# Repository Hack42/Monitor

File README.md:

# Monitor
Monitor electric power and indoor climate
Initial Version

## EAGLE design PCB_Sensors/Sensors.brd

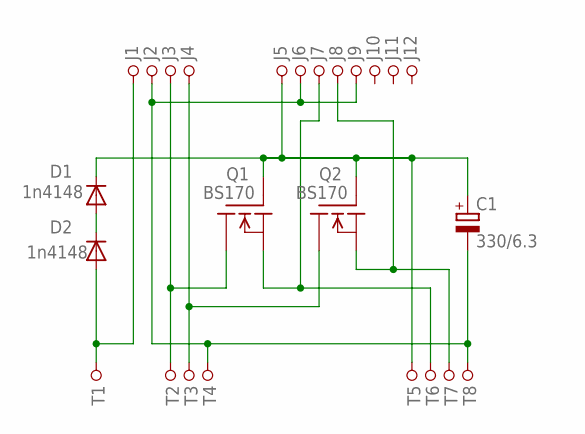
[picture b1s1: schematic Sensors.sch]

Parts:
C1: 330/6.3; E2,5-6
D1, D2: 1n4148; DO34Z7
J1, J2, J3, J4, J5, J6, J7, J8, J9, J10, J11, J12: PINHDR-1X1; HDR1X1
Q1, Q2: BS170; TO92
T1, T2, T3, T4, T5, T6, T7, T8: PINHDR-1X1; HDR1X1

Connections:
unnamed: C1.+, D1.C, J5.1, Q1.2 (G), Q2.2 (G), T5.1
unnamed: C1.-, J2.1, J6.1, J9.1, T4.1, T8.1
unnamed: D2.A, J1.1, T1.1
unnamed: D1.A, D2.C
unnamed: J3.1, Q1.3 (D), T2.1
unnamed: J4.1, Q2.3 (D), T3.1
unnamed: J7.1, Q1.1 (S), T6.1
unnamed: J8.1, Q2.1 (S), T7.1

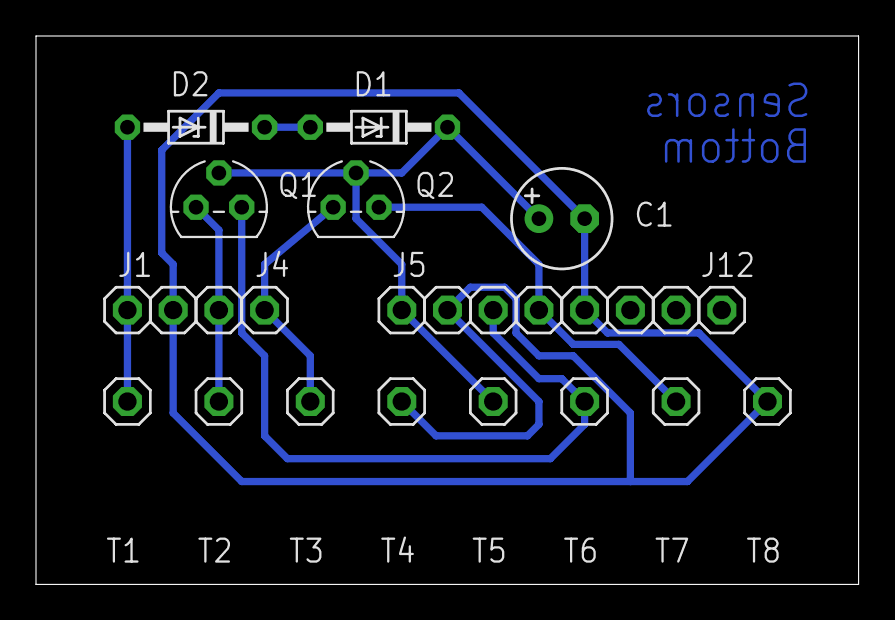
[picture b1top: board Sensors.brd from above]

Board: 1 copper layer, 45.7 x 30.5 mm, 25 parts (0 on the bottom side), 8 nets.

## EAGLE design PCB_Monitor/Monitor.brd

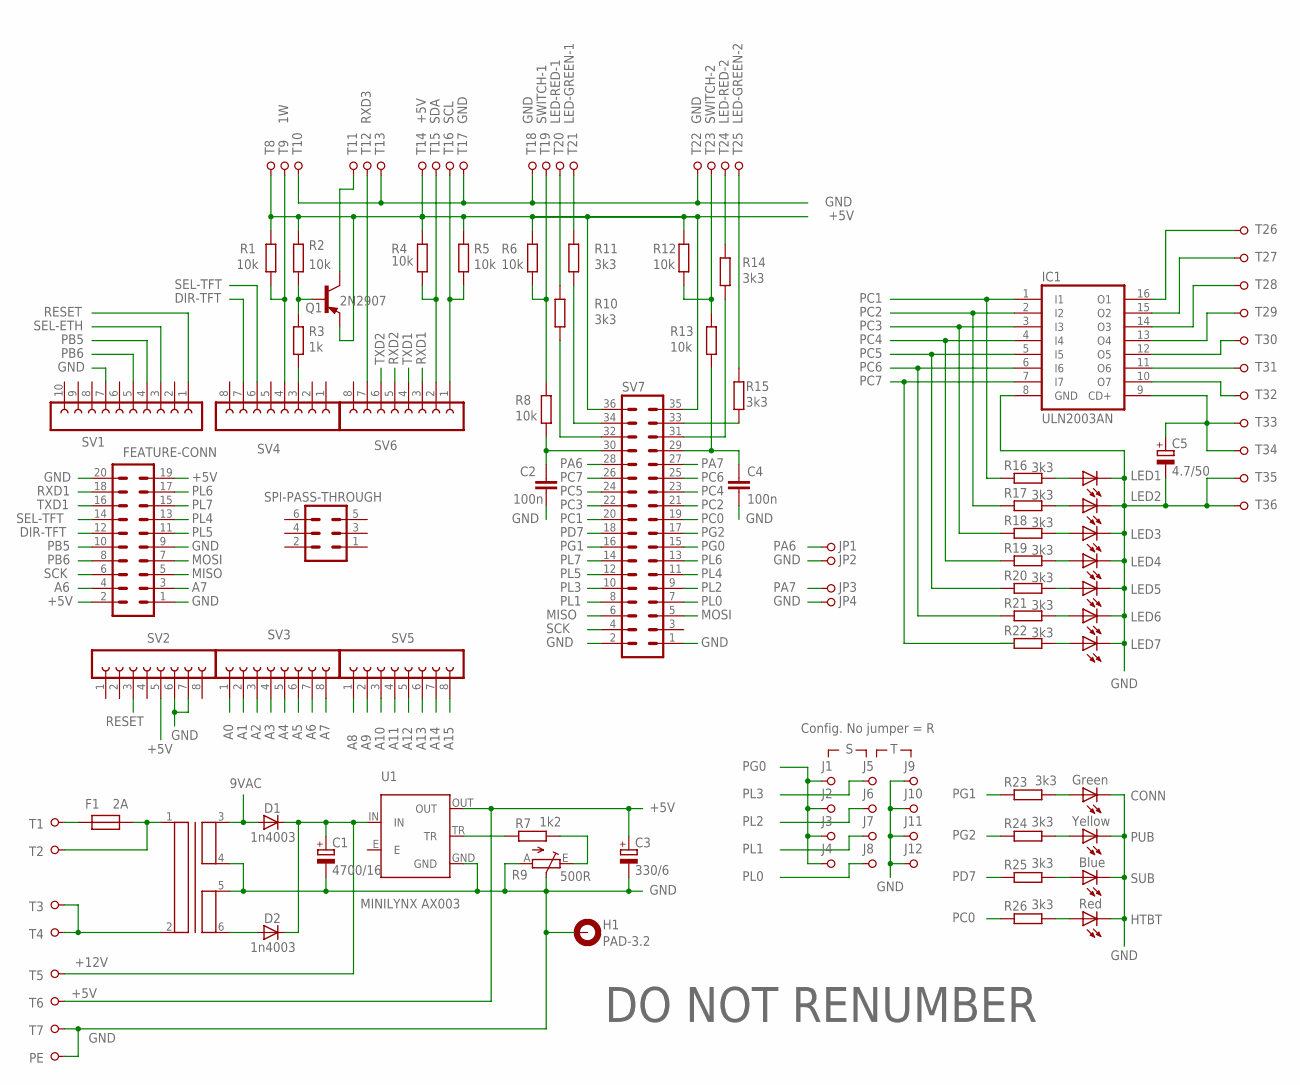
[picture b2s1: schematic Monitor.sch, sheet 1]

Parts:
C1: 4700/16; E7,5-16
C2, C4: 100n; C050-024X044
C3: 330/6; E2,5-7
C5: 4.7/50; E5-5
CONN: Green; LED3MM
D1, D2: 1n4003; DO34Z7
F1: 2A; FX0456
FEATURE-CONN: PINHD-10X2; MA10-2
H1: PAD-3.2; 3,2-PAD
HTBT: Red; LED3MM
IC1: ULN2003AN; DIL16
J1, J2, J3, J4, J5, J6, J7, J8, J9, J10, J11, J12: PINHDR-1X1; HDR1X1
JP1, JP2, JP3, JP4: PINHDR-1X1; HDR1X1
LED1, LED2, LED3, LED4, LED5, LED6, LED7: LED3MM
PE: PINHDR-1X1; HDR1X1
PUB: Yellow; LED3MM
Q1: 2N2907; TO39
R1, R2, R4, R5, R6, R8, R12, R13: 10k; 0207/10
R3: 1k; 0207/10
R7: 1k2; 0207/10
R9: 500R; TRIMPOT-4
R10, R11, R14, R15, R16, R17, R18, R19, R20, R21, R22, R23, R24, R25, R26: 3k3; 0207/10
SPI-PASS-THROUGH: PINHD-3X2; MA03-2
SUB: Blue; LED3MM
SV1: FE10-1; FE10
SV2, SV3, SV4, SV5, SV6: FE08-1; FE08
SV7: PINHD-18X2; MA18-2
T1, T2, T3, T4, T5, T6, T7, T8, T9, T10, T11, T12, T13, T14, T15, T16, T17, T18, T19, T20, T21, T22, T23, T24, T25, T26, T27, T28, T29, T30, T31, T32, T33, T34, T35, T36: PINHDR-1X1; HDR1X1
TR1: TRAFO
U1: MINILYNX AX003; MINILYNX

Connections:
1W: R1.2, SV4.4, T9.1
9VAC: D1.A, TR1.3; also elsewhere on the board
+5V: C3.+, FEATURE-CONN.2, FEATURE-CONN.19, Q1.1 (E), R1.1, R2.1, R4.1, R5.1, R6.1, R12.1, SV2.5, SV7.35, SV7.36, T6.1, T8.1, T14.1, U1.OUT; also elsewhere on the board
+12V: C1.+, D1.C, D2.C, T5.1, U1.IN; also elsewhere on the board
A0: SV3.1
A1: SV3.2
A2: SV3.3
A3: SV3.4
A4: SV3.5
A5: SV3.6
A6: FEATURE-CONN.4, SV3.7
A7: FEATURE-CONN.3, SV3.8
A8: SV5.1; also elsewhere on the board
A9: SV5.2; also elsewhere on the board
A10: SV5.3; also elsewhere on the board
A11: SV5.4; also elsewhere on the board
A12: SV5.5; also elsewhere on the board
A13: SV5.6; also elsewhere on the board
A14: SV5.7; also elsewhere on the board
A15: SV5.8; also elsewhere on the board
DIR-TFT: FEATURE-CONN.12, SV4.7
GND: C1.-, C2.1, C3.-, C4.2, C5.-, CONN.K (C), FEATURE-CONN.1, FEATURE-CONN.9, FEATURE-CONN.20, H1.B3,2, HTBT.K (C), IC1.8 (GND), J9.1, J10.1, J11.1, J12.1, JP2.1, JP4.1, LED1.K (C), LED2.K (C), LED3.K (C), LED4.K (C), LED5.K (C), LED6.K (C), LED7.K (C), PE.1, PUB.K (C), R9.A, R9.S1 (S), R9.S2 (S), SUB.K (C), SV1.7, SV2.6, SV2.7, SV7.1, SV7.2, T7.1, T10.1, T13.1, T17.1, T18.1, T22.1, T35.1, T36.1, TR1.4, TR1.5, U1.GND; also elsewhere on the board
LED-GREEN-1: R11.1, T21.1
LED-GREEN-2: R15.1, T25.1
LED-RED-1: R10.1, T20.1
LED-RED-2: R14.1, T24.1
MISO: FEATURE-CONN.5, SV7.6
MOSI: FEATURE-CONN.7, SV7.5
unnamed: LED6.A, R21.1
unnamed: R11.2, SV7.34
unnamed: R10.2, SV7.32
unnamed: C2.2, R8.2, SV7.30
unnamed: Q1.3 (C), T11.1
unnamed: R15.2, SV7.33
unnamed: R14.2, SV7.31
unnamed: R7.2, U1.TR
unnamed: IC1.15 (O2), T27.1
unnamed: LED1.A, R16.1
unnamed: LED2.A, R17.1
unnamed: LED3.A, R18.1
unnamed: LED4.A, R19.1
unnamed: LED5.A, R20.1
unnamed: LED7.A, R22.1
unnamed: C5.+, IC1.9 (CD+), T33.1, T34.1
unnamed: IC1.10 (O7), T32.1
unnamed: IC1.11 (O6), T31.1
unnamed: IC1.12 (O5), T30.1
unnamed: IC1.13 (O4), T29.1
unnamed: IC1.14 (O3), T28.1
unnamed: C4.1, R13.2, SV7.29
unnamed: IC1.16 (O1), T26.1
unnamed: D2.A, TR1.6
unnamed: F1.P$1 (1), T1.1
unnamed: F1.P$2 (2), T2.1, TR1.1
unnamed: T3.1, T4.1, TR1.2
unnamed: CONN.A, R23.1
unnamed: HTBT.A, R26.1
unnamed: R7.1, R9.E
unnamed: R3.2, SV4.3
unnamed: Q1.2 (B), R2.2, R3.1
unnamed: PUB.A, R24.1
unnamed: R25.1, SUB.A
PA6: JP1.1, SV7.28
PA7: JP3.1, SV7.27
PB5: FEATURE-CONN.10, SV1.4
PB6: FEATURE-CONN.8, SV1.5
PC0: R26.2, SV7.19
PC1: IC1.1 (I1), R16.2, SV7.20
PC2: IC1.2 (I2), R17.2, SV7.21
PC3: IC1.3 (I3), R18.2, SV7.22
PC4: IC1.4 (I4), R19.2, SV7.23
PC5: IC1.5 (I5), R20.2, SV7.24
PC6: IC1.6 (I6), R21.2, SV7.25
PC7: IC1.7 (I7), R22.2, SV7.26
PD7: R25.2, SV7.18
PG0: J1.1, J2.1, J3.1, J4.1, SV7.15
PG1: R23.2, SV7.16
PG2: R24.2, SV7.17
PL0: J8.1, SV7.7
PL1: J7.1, SV7.8
PL2: J6.1, SV7.9
PL3: J5.1, SV7.10
PL4: FEATURE-CONN.13, SV7.11
PL5: FEATURE-CONN.11, SV7.12
PL6: FEATURE-CONN.17, SV7.13
PL7: FEATURE-CONN.15, SV7.14
RESET: SV1.1, SV2.3
RXD1: FEATURE-CONN.18, SV6.3
RXD2: SV6.5
RXD3: SV6.7, T12.1
SCK: FEATURE-CONN.6, SV7.4
SCL: R5.2, SV6.1, T16.1
SDA: R4.2, SV6.2, T15.1
SEL-ETH: SV1.3
SEL-TFT: FEATURE-CONN.14, SV4.6
SWITCH-1: R6.2, R8.1, T19.1
SWITCH-2: R12.2, R13.1, T23.1
TXD1: FEATURE-CONN.16, SV6.4
TXD2: SV6.6

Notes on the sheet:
Config. No jumper = R
DO NOT RENUMBER

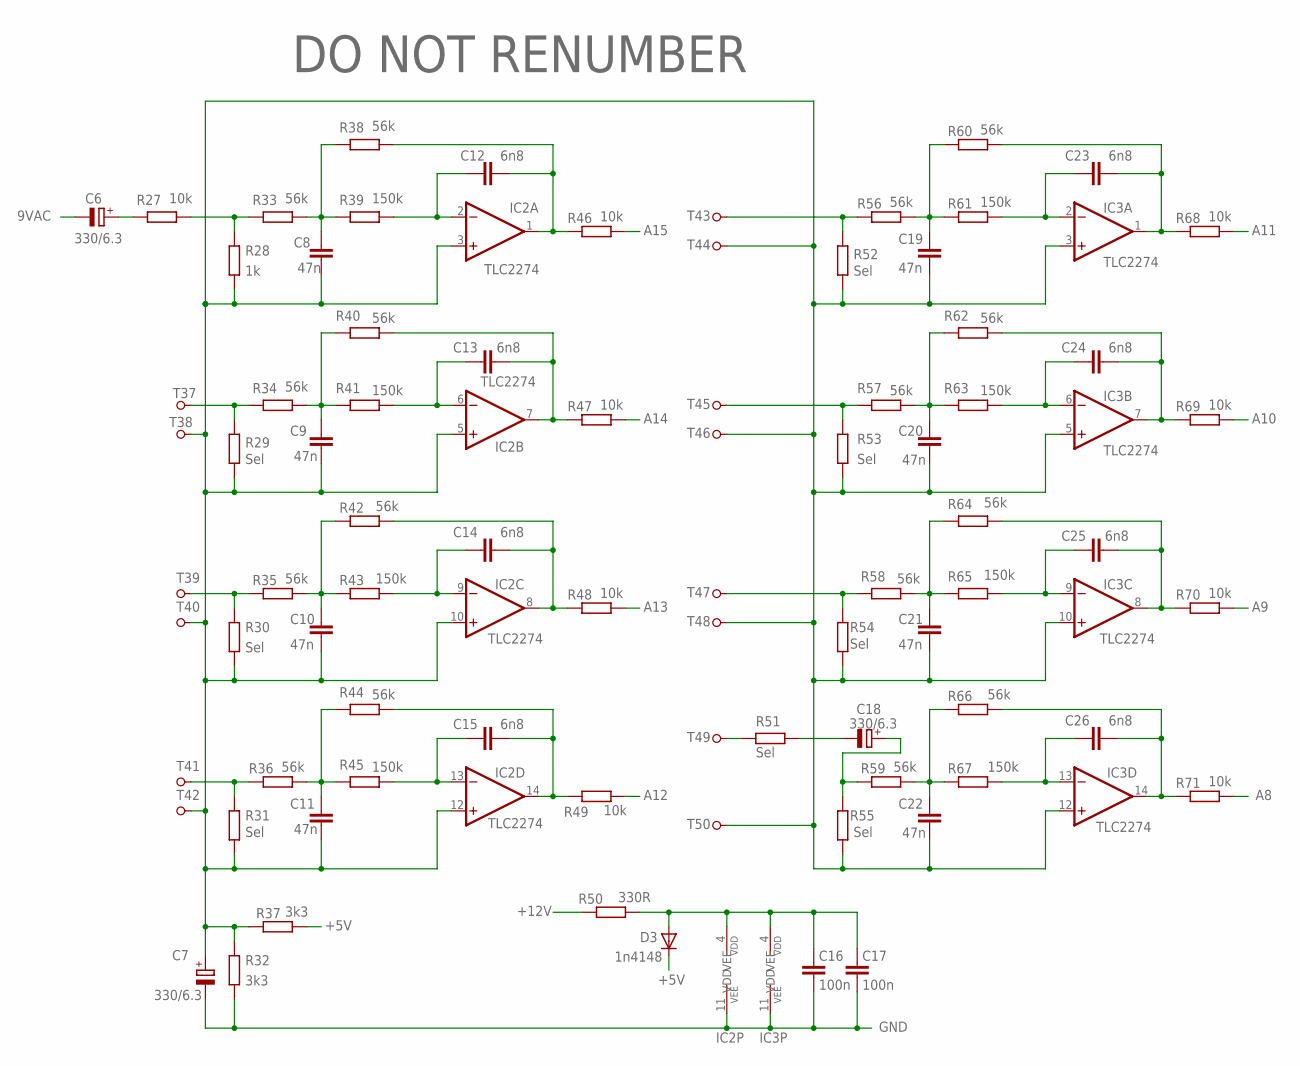
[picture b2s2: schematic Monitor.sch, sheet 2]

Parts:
C6, C7, C18: 330/6.3; E2,5-7
C8, C9, C10, C11, C19, C20, C21, C22: 47n; C050-025X075
C12, C13, C14, C15, C23, C24, C25, C26: 6n8; C050-025X075
C16, C17: 100n; C050-024X044
D3: 1n4148; DO34Z7
IC2, IC3: TLC2274; DIL14
R27, R46, R47, R48, R49, R68, R69, R70, R71: 10k; 0207/10
R28: 1k; 0207/10
R29, R30, R31, R51, R52, R53, R54, R55: Sel; 0207/10
R32, R37: 3k3; 0207/10
R33, R34, R35, R36, R38, R40, R42, R44, R56, R57, R58, R59, R60, R62, R64, R66: 56k; 0207/10
R39, R41, R43, R45, R61, R63, R65, R67: 150k; 0207/10
R50: 330R; 0207/10
T37, T38, T39, T40, T41, T42, T43, T44, T45, T46, T47, T48, T49, T50: PINHDR-1X1; HDR1X1

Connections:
9VAC: C6.-; also elsewhere on the board
+5V: D3.C, R37.2; also elsewhere on the board
+12V: R50.2; also elsewhere on the board
A8: R71.1; also elsewhere on the board
A9: R70.1; also elsewhere on the board
A10: R69.1; also elsewhere on the board
A11: R68.1; also elsewhere on the board
A12: R49.1; also elsewhere on the board
A13: R48.1; also elsewhere on the board
A14: R47.1; also elsewhere on the board
A15: R46.1; also elsewhere on the board
GND: C7.-, C16.2, C17.2, IC2.11 (VEE), IC3.11 (VEE), R32.2; also elsewhere on the board
unnamed: R27.1, R28.2, R33.2
unnamed: R30.2, R35.2, T39.1
unnamed: R31.2, R36.2, T41.1
unnamed: C6.+, R27.2
unnamed: R51.1, T49.1
unnamed: C18.-, R51.2
unnamed: C8.1, R33.1, R38.2, R39.2
unnamed: C9.1, R34.1, R40.2, R41.2
unnamed: C12.1, IC2.2 (-IN), R39.1
unnamed: C13.1, IC2.6 (-IN), R41.1
unnamed: C7.+, C8.2, C9.2, C10.2, C11.2, C19.2, C20.2, C21.2, C22.2, IC2.3 (+IN), IC2.5 (+IN), IC2.10 (+IN), IC2.12 (+IN), IC3.3 (+IN), IC3.5 (+IN), IC3.10 (+IN), IC3.12 (+IN), R28.1, R29.1, R30.1, R31.1, R32.1, R37.1, R52.1, R53.1, R54.1, R55.1, T38.1, T40.1, T42.1, T44.1, T46.1, T48.1, T50.1
unnamed: C14.2, IC2.8 (OUT), R42.1, R48.2
unnamed: C12.2, IC2.1 (OUT), R38.1, R46.2
unnamed: C19.1, R56.1, R60.2, R61.2
unnamed: C10.1, R35.1, R42.2, R43.2
unnamed: C23.1, IC3.2 (-IN), R61.1
unnamed: C15.2, IC2.14 (OUT), R44.1, R49.2
unnamed: C20.1, R57.1, R62.2, R63.2
unnamed: C14.1, IC2.9 (-IN), R43.1
unnamed: C24.1, IC3.6 (-IN), R63.1
unnamed: C11.1, R36.1, R44.2, R45.2
unnamed: C24.2, IC3.7 (OUT), R62.1, R69.2
unnamed: C21.1, R58.1, R64.2, R65.2
unnamed: C15.1, IC2.13 (-IN), R45.1
unnamed: C25.2, IC3.8 (OUT), R64.1, R70.2
unnamed: C25.1, IC3.9 (-IN), R65.1
unnamed: C22.1, R59.1, R66.2, R67.2
unnamed: C26.1, IC3.13 (-IN), R67.1
unnamed: C26.2, IC3.14 (OUT), R66.1, R71.2
unnamed: R53.2, R57.2, T45.1
unnamed: R52.2, R56.2, T43.1
unnamed: R54.2, R58.2, T47.1
unnamed: C18.+, R55.2, R59.2
unnamed: C16.1, C17.1, D3.A, IC2.4 (VDD), IC3.4 (VDD), R50.1
unnamed: C23.2, IC3.1 (OUT), R60.1, R68.2
unnamed: R29.2, R34.2, T37.1
unnamed: C13.2, IC2.7 (OUT), R40.1, R47.2

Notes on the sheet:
DO NOT RENUMBER

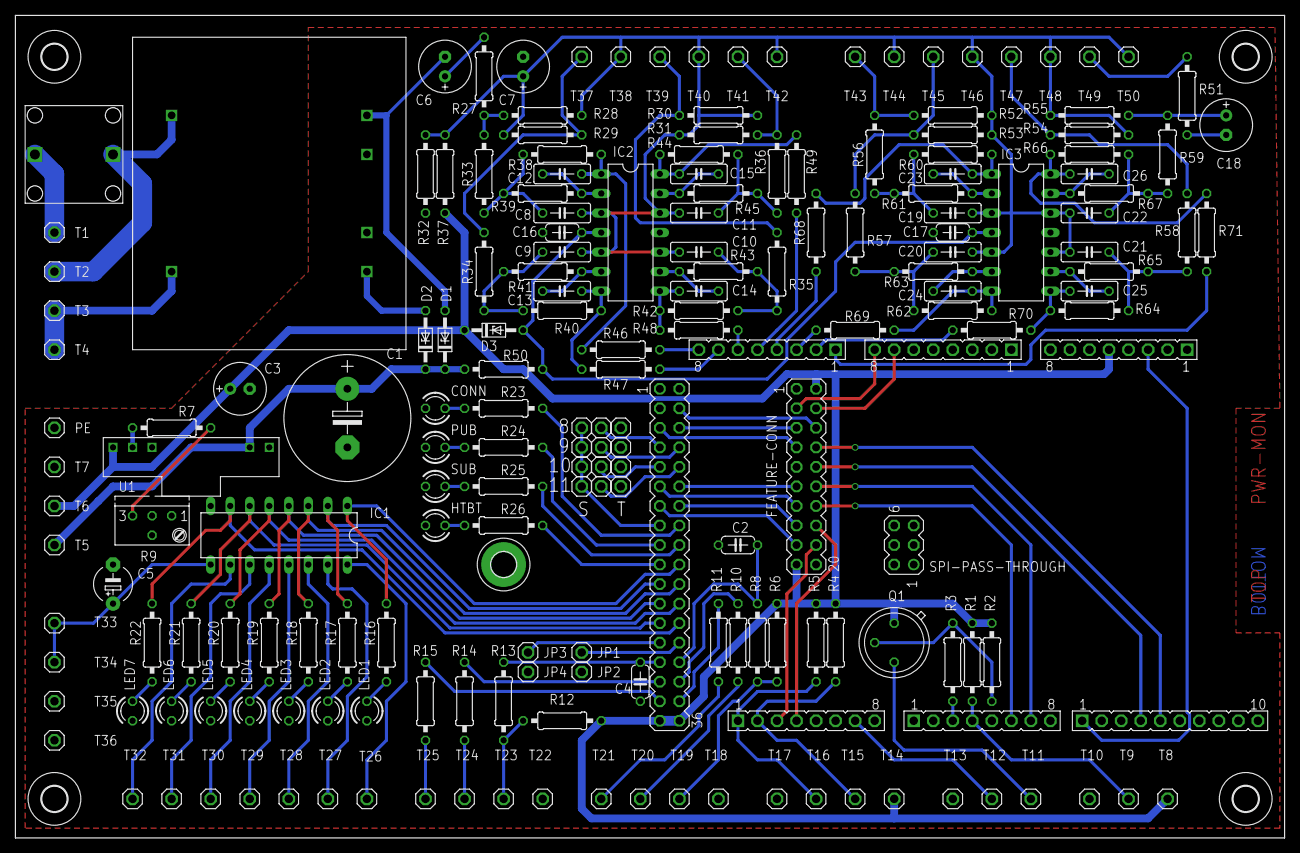
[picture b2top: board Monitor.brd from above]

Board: 2 copper layers, 165.1 x 107.0 mm, 199 parts (0 on the bottom side), 127 nets.

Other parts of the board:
U$2, U$3, U$4, U$5: 3,3
